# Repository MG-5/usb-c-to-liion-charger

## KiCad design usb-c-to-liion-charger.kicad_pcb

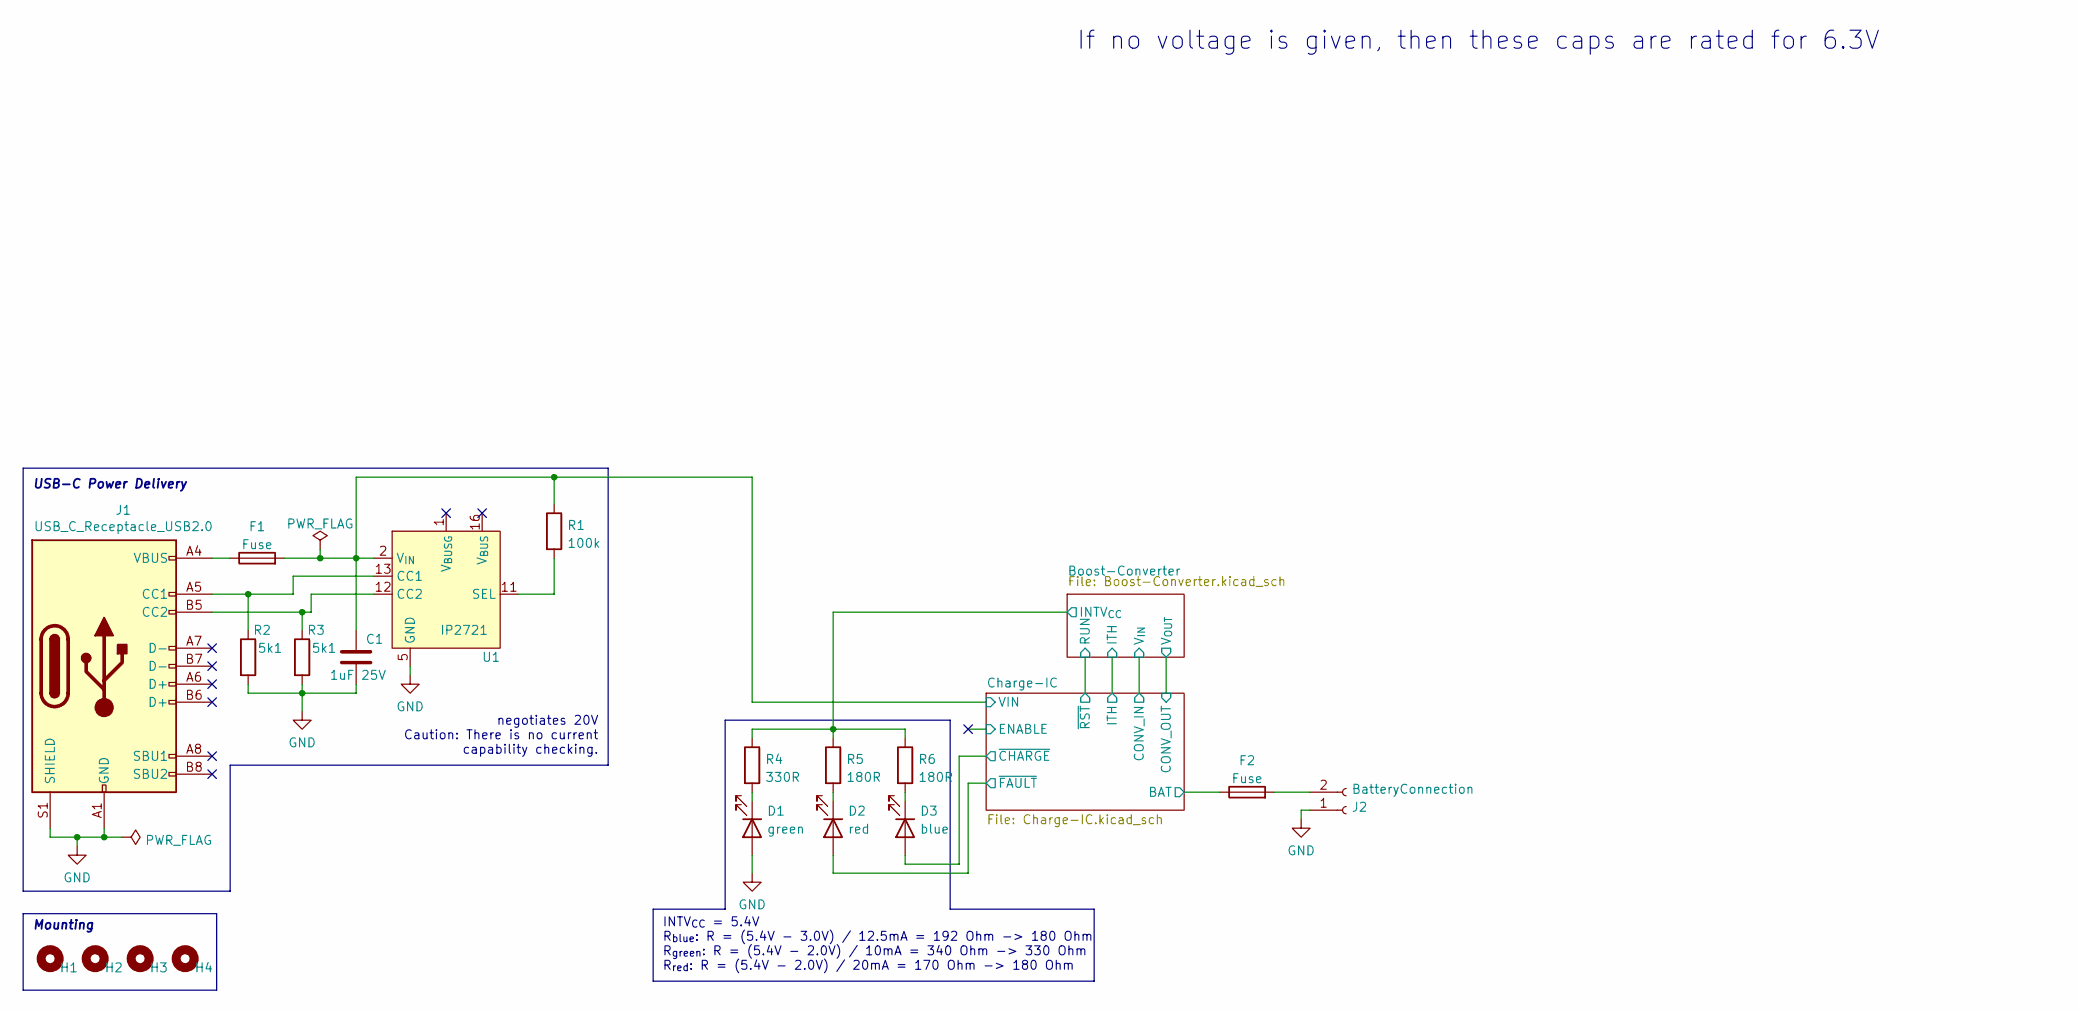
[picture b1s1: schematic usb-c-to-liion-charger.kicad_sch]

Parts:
C1: 1uF 25V; C_0603_1608Metric
D1: green; LED_0603_1608Metric
D2: red; LED_0603_1608Metric
D3: blue; LED_0603_1608Metric
F1, F2: Fuse; KEYSTONE-FUSE-3557-2
H1, H2, H3, H4: MountingHole_3.2mm_M3_ISO7380_Keepout
J1: USB_C_Receptacle_USB2.0; USB_C_Receptacle_Palconn_UTC16-G
J2: BatteryConnection; AMASS_XT30U-M_1x02_P5.0mm_Vertical
R1: 100k; R_0603_1608Metric
R2, R3: 5k1; R_0603_1608Metric
R4: 330R; R_0603_1608Metric
R5, R6: 180R; R_0603_1608Metric
U1: IP2721; TSSOP-16_4.4x5mm_P0.65mm

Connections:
/Boost-Converter/INTV_{CC}: R4.1, R5.1, R6.1; also elsewhere on the board
/Charge-IC/BAT: F2.1; also elsewhere on the board
/Charge-IC/VIN: C1.1, F1.2, R1.1, U1.2 (V_{IN}); also elsewhere on the board
/Charge-IC/~CHARGE: D3.2 (A); also elsewhere on the board
/Charge-IC/~FAULT: D2.2 (A); also elsewhere on the board
GND: C1.2, D1.2 (A), J1.A1 (GND), J1.A12 (GND), J1.B1 (GND), J1.B12 (GND), J1.S1 (SHIELD), J2.1, R2.2, R3.2, U1.5 (GND); also elsewhere on the board
unnamed: D1.1 (K), R4.2
unnamed: D2.1 (K), R5.2
unnamed: D3.1 (K), R6.2
unnamed: F1.1, J1.A4 (VBUS), J1.A9 (VBUS), J1.B4 (VBUS), J1.B9 (VBUS)
unnamed: J1.A5 (CC1), R2.1, U1.13 (CC1)
unnamed: J1.B5 (CC2), R3.1, U1.12 (CC2)
unnamed: F2.2, J2.2
unnamed: R1.2, U1.11 (SEL)

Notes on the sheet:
USB-C Power Delivery
If no voltage is given, then these caps are rated for 6.3V
negotiates 20V Caution: There is no current capability checking.
Mounting
INTV_{CC} = 5.4V R_{blue}: R = (5.4V - 3.0V) / 12.5mA = 192 Ohm -> 180 Ohm R_{green}: R = (5.4V - 2.0V) / 10mA = 340 Ohm -> 330 Ohm R_{red}: R = (5.4V - 2.0V) / 20mA = 170 Ohm -> 180 Ohm

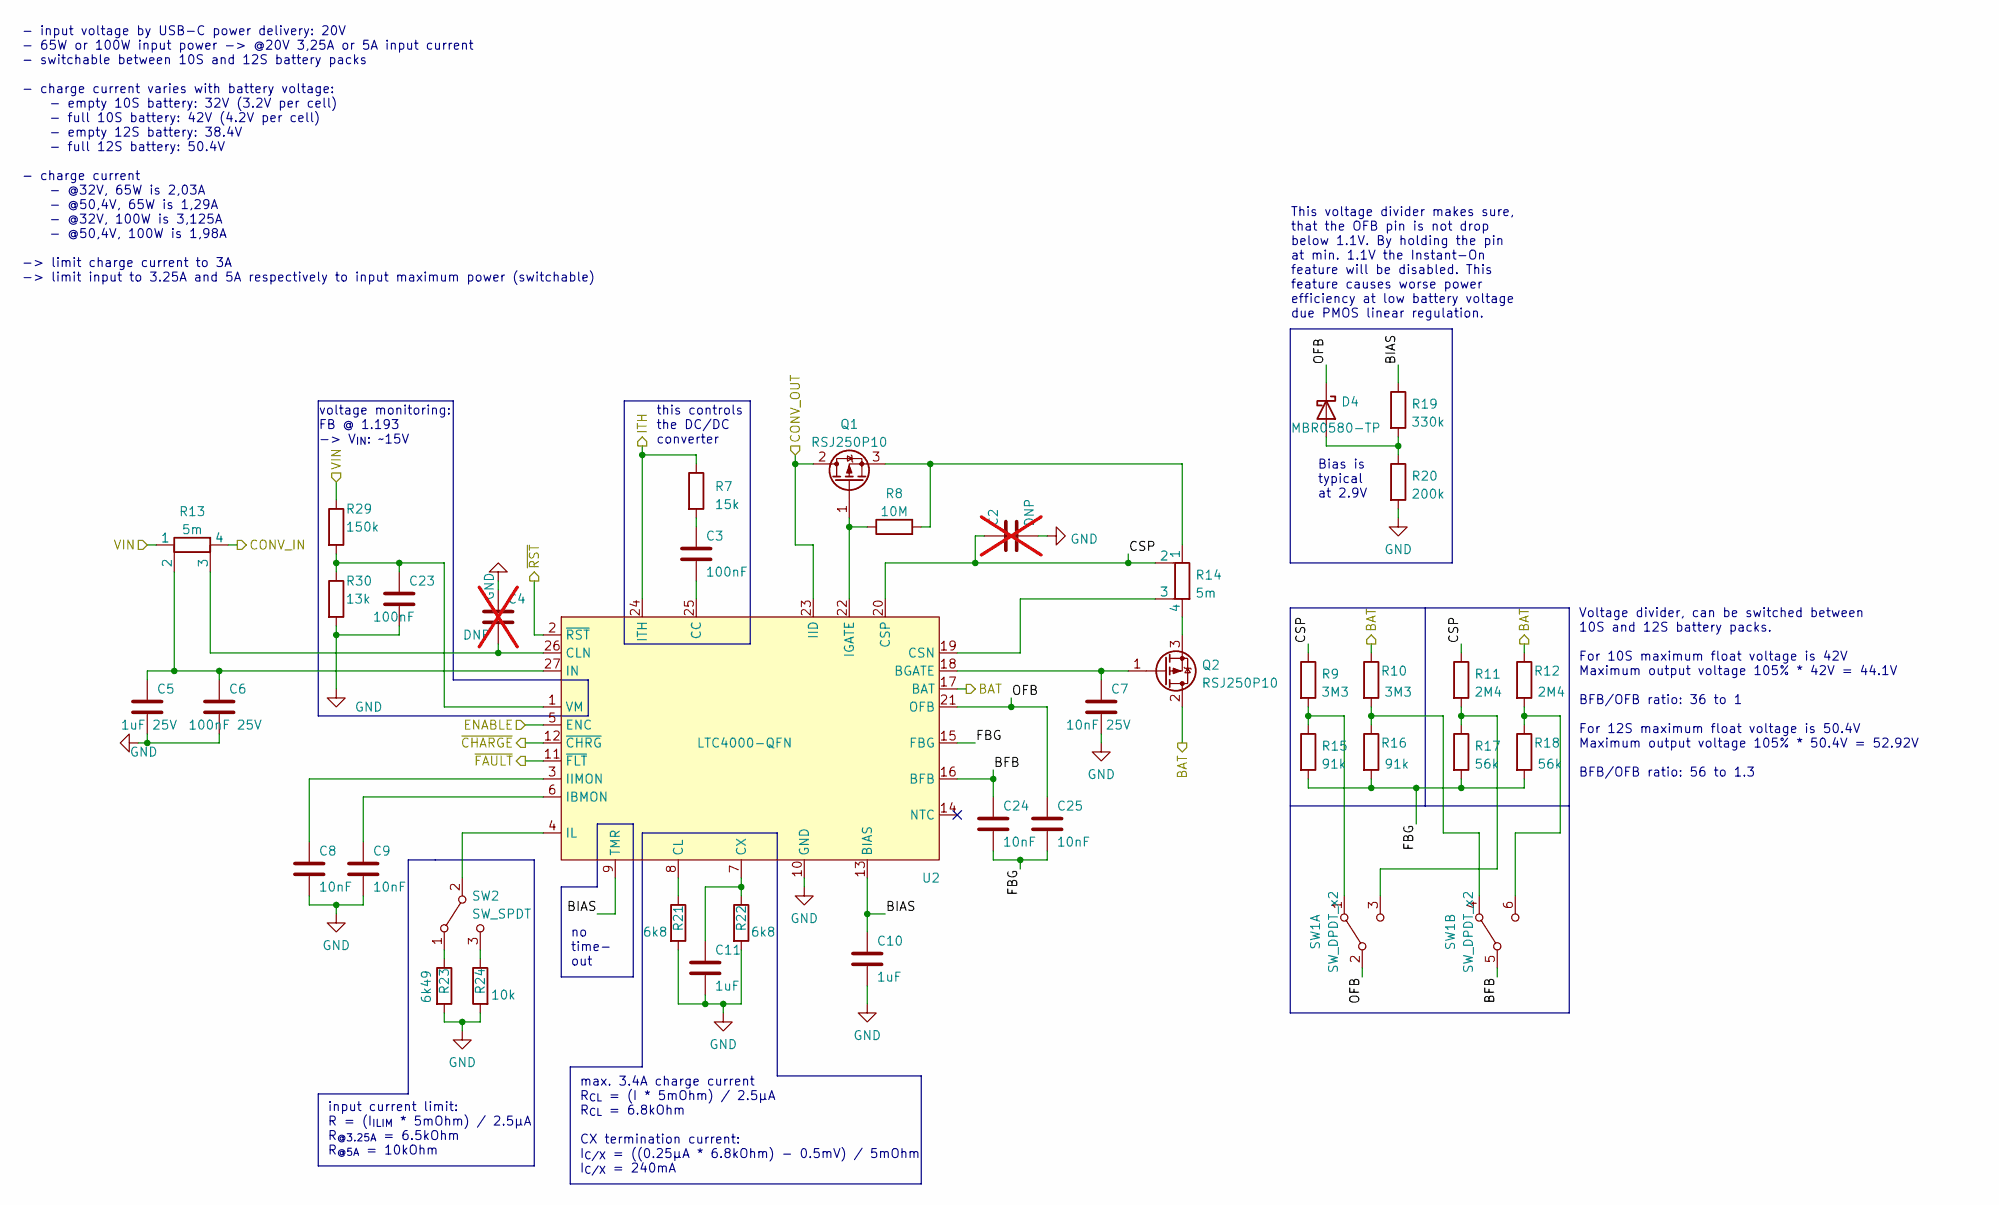
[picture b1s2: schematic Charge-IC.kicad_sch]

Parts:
C2, C4: DNP; C_0603_1608Metric; not fitted
C3, C23: 100nF; C_0603_1608Metric
C5: 1uF 25V; C_0603_1608Metric
C6: 100nF 25V; C_0603_1608Metric
C7: 10nF 25V; C_0603_1608Metric
C8, C9, C24, C25: 10nF; C_0603_1608Metric
C10, C11: 1uF; C_0603_1608Metric
D4: MBR0580-TP; D_SOD-123
Q1, Q2: RSJ250P10; TO-263-2
R7: 15k; R_0603_1608Metric
R8: 10M; R_0603_1608Metric
R9, R10: 3M3; R_0603_1608Metric
R11, R12: 2M4; R_0603_1608Metric
R13, R14: 5m; R_0805_2012Metric_4Kelvin
R15, R16: 91k; R_0603_1608Metric
R17, R18: 56k; R_0603_1608Metric
R19: 330k; R_0603_1608Metric
R20: 200k; R_0603_1608Metric
R21, R22: 6k8; R_0603_1608Metric
R23: 6k49; R_0603_1608Metric
R24: 10k; R_0603_1608Metric
R29: 150k; R_0603_1608Metric
R30: 13k; R_0603_1608Metric
SW1: SW_DPDT_x2; SW_E-Switch_EG2201_DPDT
SW2: SW_SPDT; SW_E-Switch_EG1249_SPDT
U2: LTC4000-QFN; QFN-28-1EP_4x5mm_P0.5mm_EP2.65x3.65mm_ThermalVias

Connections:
/Boost-Converter/ITH: R7.1, U2.24 (ITH); also elsewhere on the board
/Boost-Converter/RUN: U2.2 (~RST); also elsewhere on the board
/Boost-Converter/V_{IN}: R13.4; also elsewhere on the board
/Boost-Converter/V_{OUT}: Q1.2 (D), U2.23 (IID); also elsewhere on the board
/Charge-IC/BAT: Q2.2 (D), R10.1, R12.1, U2.17 (BAT); also elsewhere on the board
/Charge-IC/BFB: C24.1, SW1.5 (B), U2.16 (BFB)
/Charge-IC/BIAS: C10.1, R19.1, U2.9 (TMR), U2.13 (BIAS)
/Charge-IC/CSP: C2.1, R9.1, R11.1, R14.2, U2.20 (CSP)
/Charge-IC/ENABLE: U2.5 (ENC)
/Charge-IC/FBG: C24.2, C25.2, R15.2, R16.2, R17.2, R18.2, U2.15 (FBG)
/Charge-IC/OFB: C25.1, D4.1 (K), SW1.2 (B), U2.21 (OFB)
/Charge-IC/VIN: R13.1, R29.1; also elsewhere on the board
/Charge-IC/~CHARGE: U2.12 (~CHRG); also elsewhere on the board
/Charge-IC/~FAULT: U2.11 (~FLT); also elsewhere on the board
GND: C2.2, C4.1, C5.2, C6.2, C7.2, C8.2, C9.2, C10.2, C11.2, C23.2, R20.2, R21.2, R22.2, R23.2, R24.2, R30.2, U2.10 (GND), U2.28 (GND), U2.29 (GND); also elsewhere on the board
unnamed: C3.1, R7.2
unnamed: D4.2 (A), R19.2, R20.1
unnamed: Q1.1 (G), R8.1, U2.22 (IGATE)
unnamed: Q1.3 (S), R8.2, R14.1
unnamed: C7.1, Q2.1 (G), U2.18 (BGATE)
unnamed: Q2.3 (S), R14.4
unnamed: R9.2, R15.1, SW1.1 (A)
unnamed: R11.2, R17.1, SW1.3 (C)
unnamed: R10.2, R16.1, SW1.4 (A)
unnamed: R12.2, R18.1, SW1.6 (C)
unnamed: R23.1, SW2.1 (A)
unnamed: SW2.2 (B), U2.4 (IL)
unnamed: R24.1, SW2.3 (C)
unnamed: C3.2, U2.25 (CC)
unnamed: R21.1, U2.8 (CL)
unnamed: C4.2, R13.3, U2.26 (CLN)
unnamed: R14.3, U2.19 (CSN)
unnamed: C11.1, R22.1, U2.7 (CX)
unnamed: C9.1, U2.6 (IBMON)
unnamed: C8.1, U2.3 (IIMON)
unnamed: C5.1, C6.1, R13.2, U2.27 (IN)
unnamed: C23.1, R29.2, R30.1, U2.1 (VM)

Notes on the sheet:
no time- out
max. 3.4A charge current R_{CL} = (I * 5mOhm) / 2.5µA R_{CL} = 6.8kOhm CX termination current: I_{C/X} = ((0.25µA * 6.8kOhm) - 0.5mV) / 5mOhm I_{C/X} = 240mA
Voltage divider, can be switched between 10S and 12S battery packs. For 10S maximum float voltage is 42V Maximum output voltage 105% * 42V = 44.1V BFB/OFB ratio: 36 to 1 For 12S maximum float voltage is 50.4V Maximum output voltage 105% * 50.4V = 52.92V BFB/OFB ratio: 56 to 1.3
This voltage divider makes sure, that the OFB pin is not drop below 1.1V. By holding the pin at min. 1.1V the Instant-On feature will be disabled. This feature causes worse power efficiency at low battery voltage due PMOS linear regulation.
Bias is typical at 2.9V
this controls the DC/DC converter
voltage monitoring: FB @ 1.193 -> V_{IN}: ~15V
input current limit: R = (I_{ILIM} * 5mOhm) / 2.5µA R_{@3.25A} = 6.5kOhm R_{@5A} = 10kOhm
- input voltage by USB-C power delivery: 20V - 65W or 100W input power -> @20V 3,25A or 5A input current - switchable between 10S and 12S battery packs - charge current varies with battery voltage: - empty 10S battery: 32V (3.2V per cell) - full 10S battery: 42V (4.2V per cell) - empty 12S battery: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

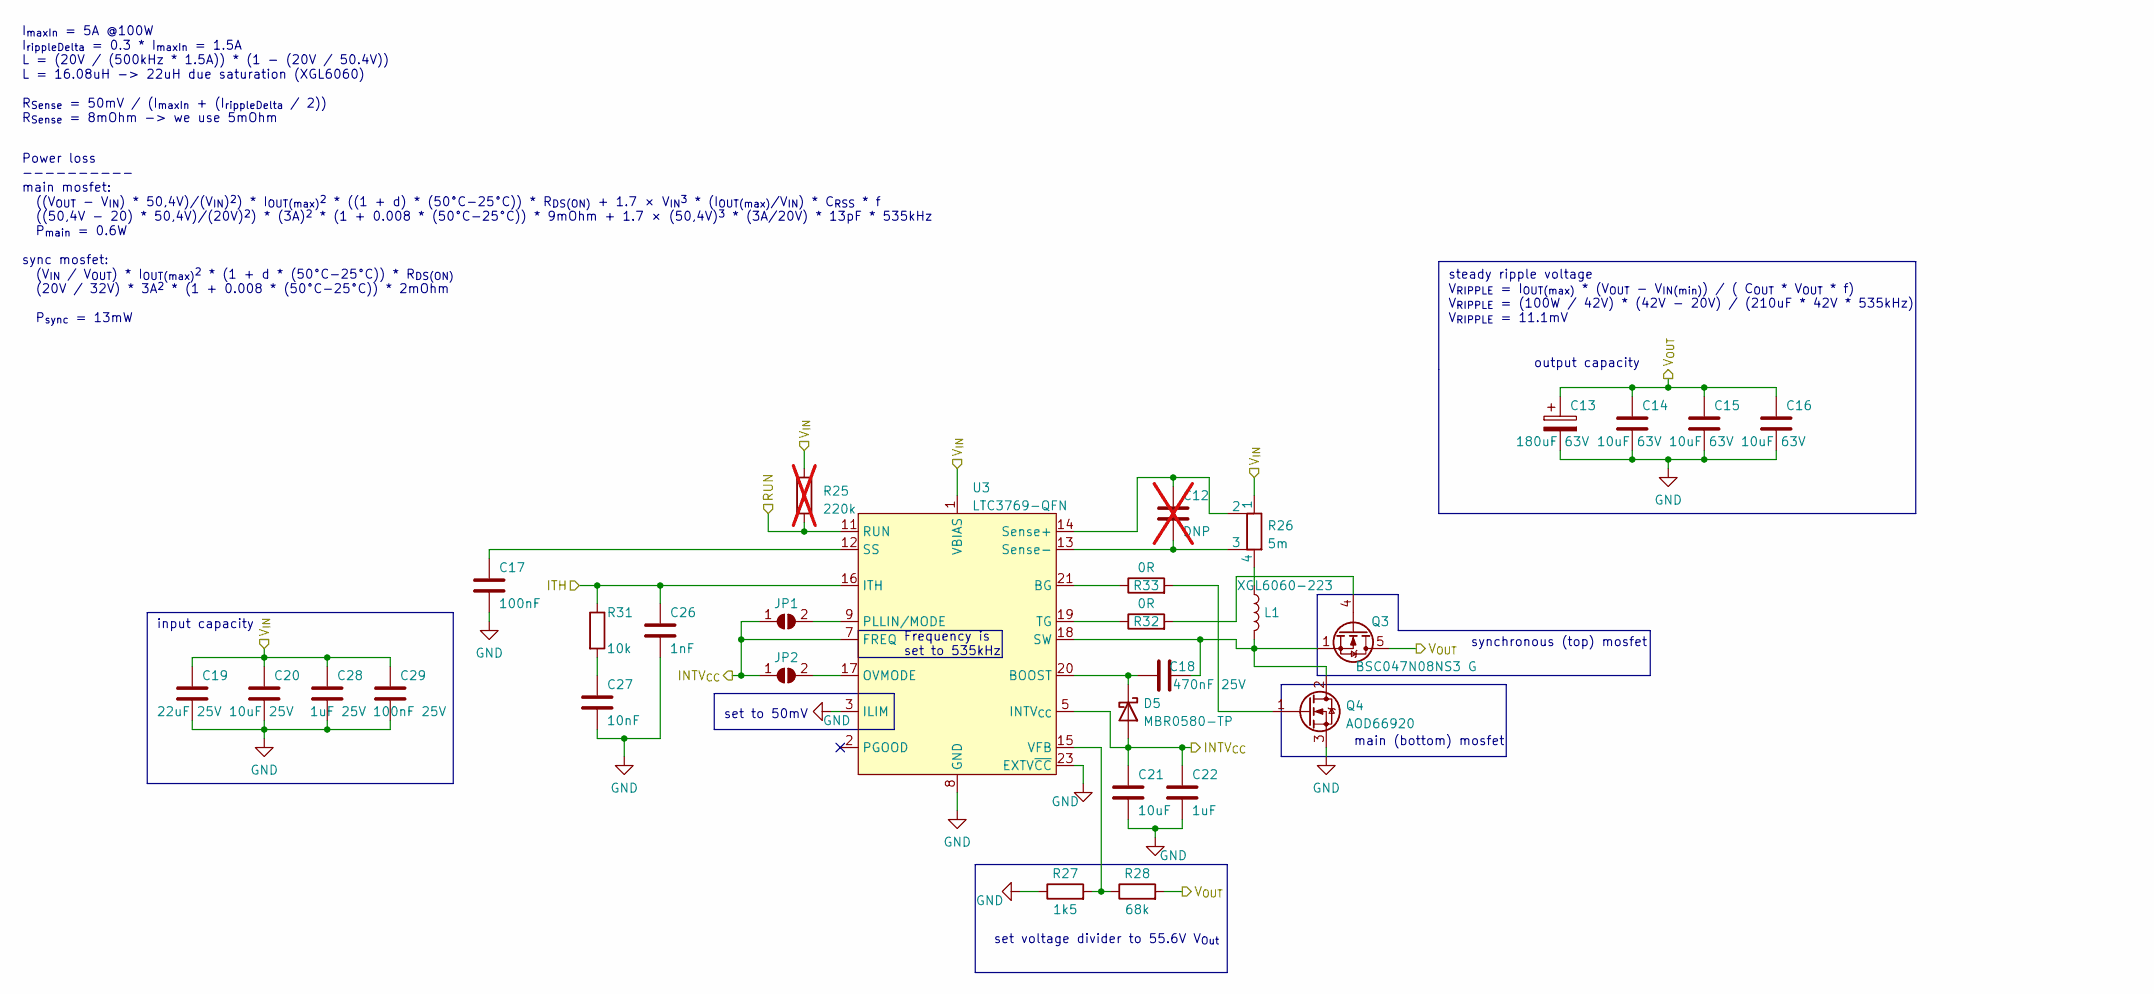
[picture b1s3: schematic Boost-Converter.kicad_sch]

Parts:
C12: DNP; C_0603_1608Metric; not fitted
C13: 180uF 63V; CP_Radial_D10.0mm_P5.00mm
C14, C15, C16: 10uF 63V; C_1210_3225Metric
C17: 100nF; C_0603_1608Metric
C18: 470nF 25V; C_0603_1608Metric
C19: 22uF 25V; C_0805_2012Metric
C20: 10uF 25V; C_0805_2012Metric
C21: 10uF; C_0805_2012Metric
C22: 1uF; C_0603_1608Metric
C26: 1nF; C_0603_1608Metric
C27: 10nF; C_0603_1608Metric
C28: 1uF 25V; C_0805_2012Metric
C29: 100nF 25V; C_0805_2012Metric
D5: MBR0580-TP; D_SOD-123
JP1, JP2: SolderJumper_2_Open; SolderJumper-Open_0603
L1: XGL6060-223; L_Coilcraft_XAL6060-XXX
Q3: BSC047N08NS3 G; TDSON-8-1
Q4: AOD66920; TO-252-3_TabPin2
R25: 220k; R_0603_1608Metric; not fitted
R26: 5m; R_0805_2012Metric_4Kelvin
R27: 1k5; R_0603_1608Metric
R28: 68k; R_0603_1608Metric
R31: 10k; R_0603_1608Metric
R32, R33: 0R; R_0603_1608Metric
U3: LTC3769-QFN; WQFN-24-1EP_4x4mm_P0.5mm_EP2.45x2.45mm_ThermalVias

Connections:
/Boost-Converter/INTV_{CC}: C21.1, C22.1, D5.2 (A), JP1.1 (A), JP2.1 (A), U3.5 (INTV_{CC}), U3.7 (FREQ), U3.22 (INTV_{CC}); also elsewhere on the board
/Boost-Converter/ITH: C26.1, R31.1, U3.16 (ITH); also elsewhere on the board
/Boost-Converter/RUN: R25.2, U3.11 (RUN); also elsewhere on the board
/Boost-Converter/V_{IN}: C19.1, C20.1, C28.1, C29.1, R25.1, R26.1, U3.1 (VBIAS); also elsewhere on the board
/Boost-Converter/V_{OUT}: C13.1, C14.1, C15.1, C16.1, Q3.5 (D), R28.2; also elsewhere on the board
GND: C13.2, C14.2, C15.2, C16.2, C17.2, C19.2, C20.2, C21.2, C22.2, C26.2, C27.2, C28.2, C29.2, Q4.3 (S), R27.1, U3.3 (ILIM), U3.8 (GND), U3.10 (GND), U3.23 (EXTV~CC), U3.24 (GND), U3.25 (GND); also elsewhere on the board
unnamed: C27.1, R31.2
unnamed: C18.2, D5.1 (K), U3.20 (BOOST)
unnamed: JP1.2 (B), U3.9 (PLLIN/MODE)
unnamed: JP2.2 (B), U3.17 (OVMODE)
unnamed: L1.1, R26.4
unnamed: Q3.4 (G), R32.2
unnamed: C18.1, L1.2, Q3.1 (S), Q3.2 (S), Q3.3 (S), Q4.2 (D), U3.18 (SW)
unnamed: Q4.1 (G), R33.2
unnamed: R33.1, U3.21 (BG)
unnamed: C17.1, U3.12 (SS)
unnamed: C12.1, R26.2, U3.14 (Sense+)
unnamed: C12.2, R26.3, U3.13 (Sense-)
unnamed: R32.1, U3.19 (TG)
unnamed: R27.2, R28.1, U3.15 (VFB)

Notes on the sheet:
Power loss ---------- main mosfet: ((V_{OUT} − V_{IN}) * 50,4V)/(V_{IN})^{2}) * I_{OUT(max)}^{2} * ((1 + d) * (50°C-25°C)) * R_{DS(ON)} + 1.7 × V_{IN}^{3} * (I_{OUT(max)}/V_{IN}) * C_{RSS} * f ((50,4V − 20) * 50,4V)/(20V)^{2}) * (3A)^{2} * (1 + 0.008 * (50°C-25°C)) * 9mOhm + 1.7 × (50,4V)^{3} * (3A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
steady ripple voltage V_{RIPPLE} = I_{OUT(max)} * (V_{OUT} - V_{IN(min)}) / ( C_{OUT} * V_{OUT} * f) V_{RIPPLE} = (100W / 42V) * (42V - 20V) / (210uF * 42V * 535kHz) V_{RIPPLE} = 11.1mV
I_{maxIn} = 5A @100W I_{rippleDelta} = 0.3 * I_{maxIn} = 1.5A L = (20V / (500kHz * 1.5A)) * (1 - (20V / 50.4V)) L = 16.08uH -> 22uH due saturation (XGL6060) R_{Sense} = 50mV / (I_{maxIn} + (I_{rippleDelta} / 2)) R_{Sense} = 8mOhm -> we use 5mOhm
input capacity
output capacity
main (bottom) mosfet
set to 50mV
set voltage divider to 55.6V V_{Out}
Frequency is set to 535kHz
synchronous (top) mosfet

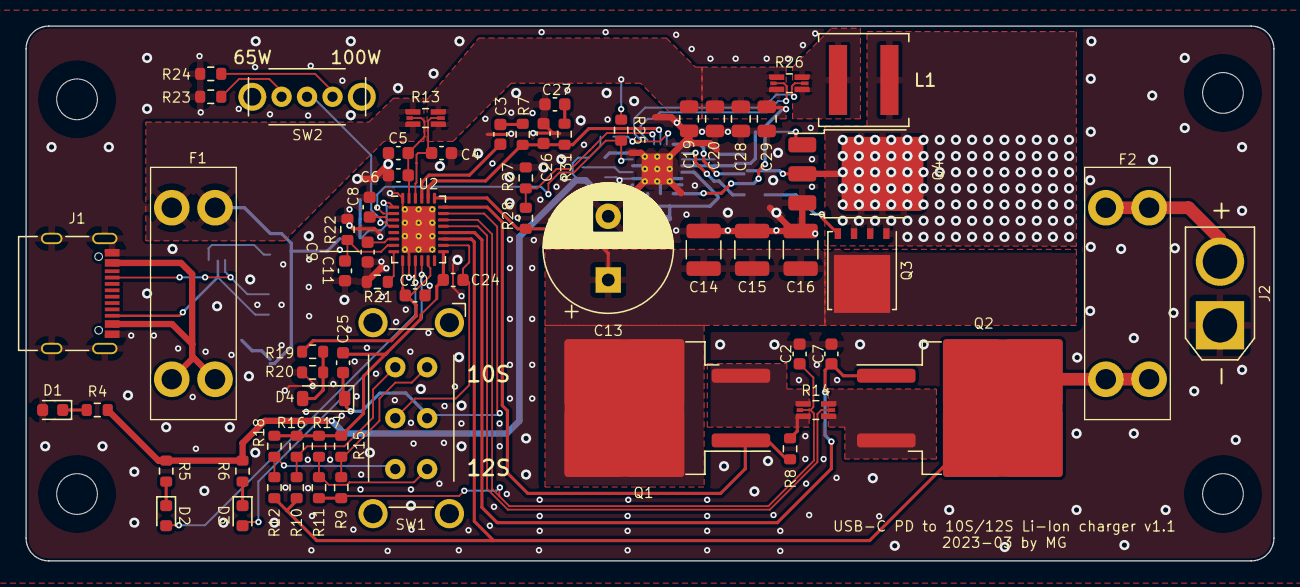
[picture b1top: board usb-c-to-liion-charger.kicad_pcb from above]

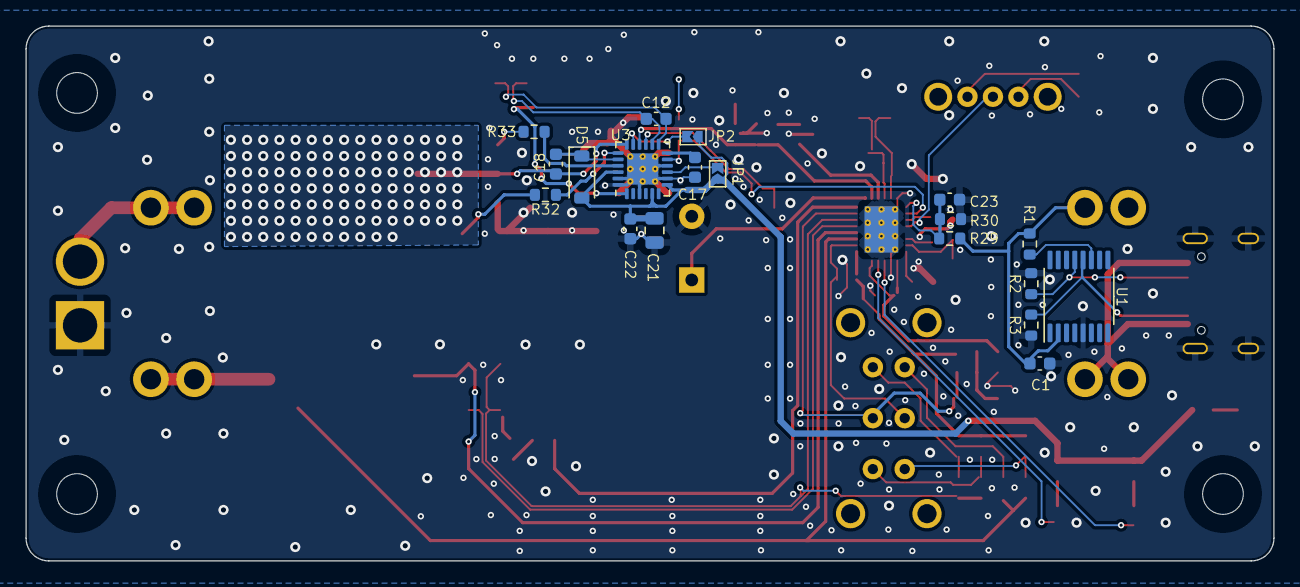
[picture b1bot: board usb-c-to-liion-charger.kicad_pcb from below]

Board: 2 copper layers, 98.0 x 42.0 mm, 87 parts (19 on the bottom side), 59 nets.

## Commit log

2022-03-24 Convert symbol lib to new version
2022-03-24 Add LTC4000 and LTC3789
2022-03-30 WIP charge IC
2022-03-30 Finish Charge IC, WIP boost converter, add LTC3769
2022-04-01 WIP boost converter
2022-04-01 Finish boost converter
2022-04-04 Finish schematic
2022-04-04 Small changes
2022-04-07 Annotate symbols and assign footprints
2022-04-07 Add mounting holes
2022-04-09 [WIP] Start PCB
2022-05-10 Finish PCB
2022-05-16 Optimize ground vias
2022-05-16 Add BOM
2022-05-16 Update BOM due component order
2022-05-22 Add settings for Gerber
2022-09-29 Create LICENSE
2023-03-03 Update to KiCad 7
2023-03-04 Fix wrong battery polarity Enable voltage monitoring at 15V Add caps to OFB and BFB Use another diodes Replace 1206 shunt with 0805 Replace main mosfet with bigger one Improve traces/ground planes
2023-03-08 Small changes due gerber export
2023-06-14 Add notes for lower switching frequency
